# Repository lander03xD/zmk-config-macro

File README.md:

# macr03xD

## What is it?

This project is handwired macropad.

Project firmware is using [ZMK](https://zmk.dev).
The case and plate are modelled with [FreeCAD](https://www.freecad.org/).

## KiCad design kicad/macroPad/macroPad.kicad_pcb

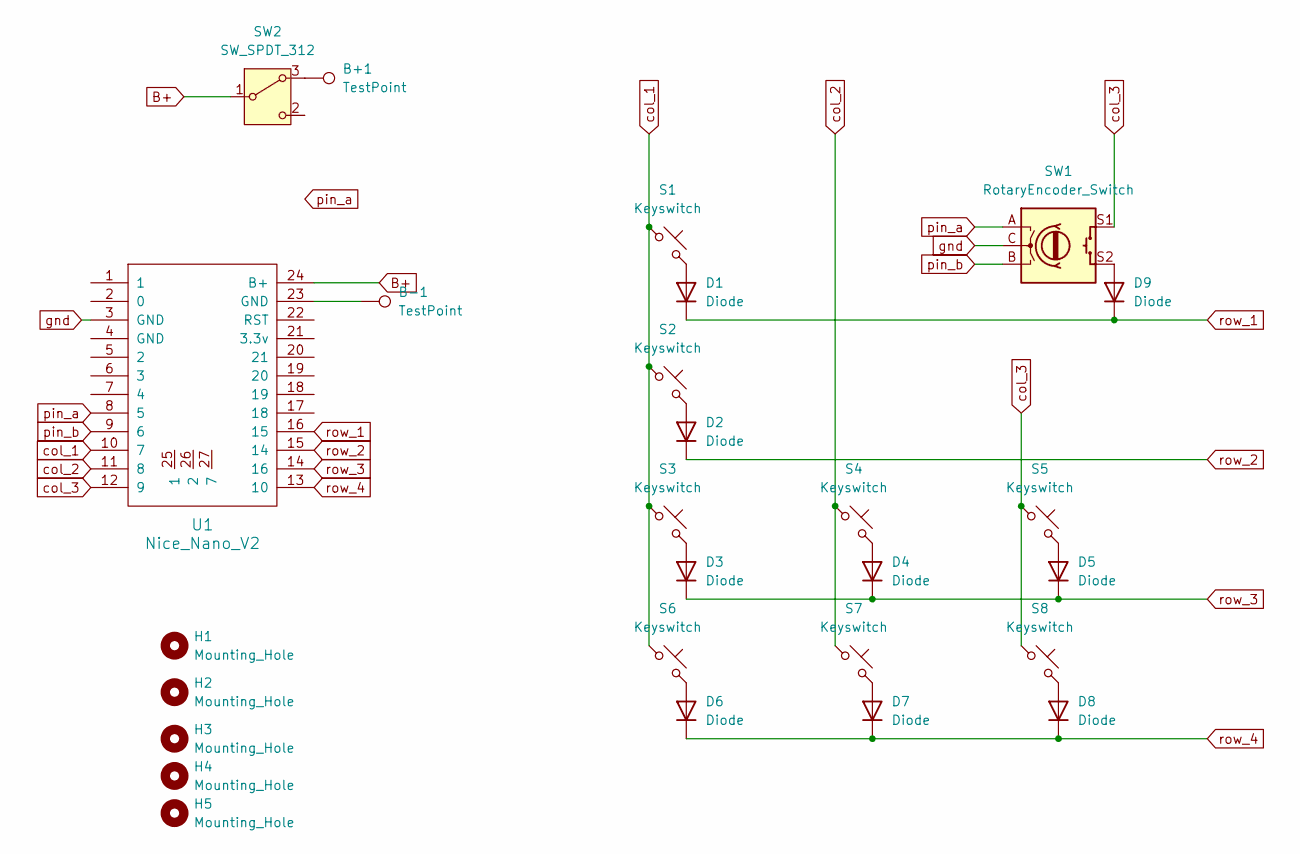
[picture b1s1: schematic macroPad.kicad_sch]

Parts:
B+1: TestPoint
B-1: TestPoint
D1, D2, D3, D4, D5, D6, D7, D8, D9: Diode; Diode_DO-35
H1, H2, H3, H4, H5: Mounting_Hole; MountingHole_2.2mm_M2
S1, S2, S3, S4, S5, S6, S7, S8: Keyswitch; MX_Solder_1.00u
SW1: RotaryEncoder_Switch; Encoder_EC11_MX
SW2: SW_SPDT_312; SW_Vertical_Slide_5mm
U1: Nice_Nano_V2

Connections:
B+: SW2.1 (B), U1.24 (B+)
unnamed: B-1.1, U1.23 (GND)
unnamed: D1.2 (A), S1.2
unnamed: D2.2 (A), S2.2
unnamed: D3.2 (A), S3.2
unnamed: D4.2 (A), S4.2
unnamed: D5.2 (A), S5.2
unnamed: D6.2 (A), S6.2
unnamed: D7.2 (A), S7.2
unnamed: D8.2 (A), S8.2
unnamed: D9.2 (A), SW1.S2
unnamed: B+1.1, SW2.3 (A)
col_1: S1.1, S2.1, S3.1, S6.1, U1.10 (7)
col_2: S4.1, S7.1, U1.11 (8)
col_3: S5.1, S8.1, SW1.S1, U1.12 (9)
gnd: SW1.C, U1.3 (GND)
pin_a: SW1.A, U1.8 (5)
pin_b: SW1.B, U1.9 (6)
row_1: D1.1 (K), D9.1 (K), U1.16 (15)
row_2: D2.1 (K), U1.15 (14)
row_3: D3.1 (K), D4.1 (K), D5.1 (K), U1.14 (16)
row_4: D6.1 (K), D7.1 (K), D8.1 (K), U1.13 (10)

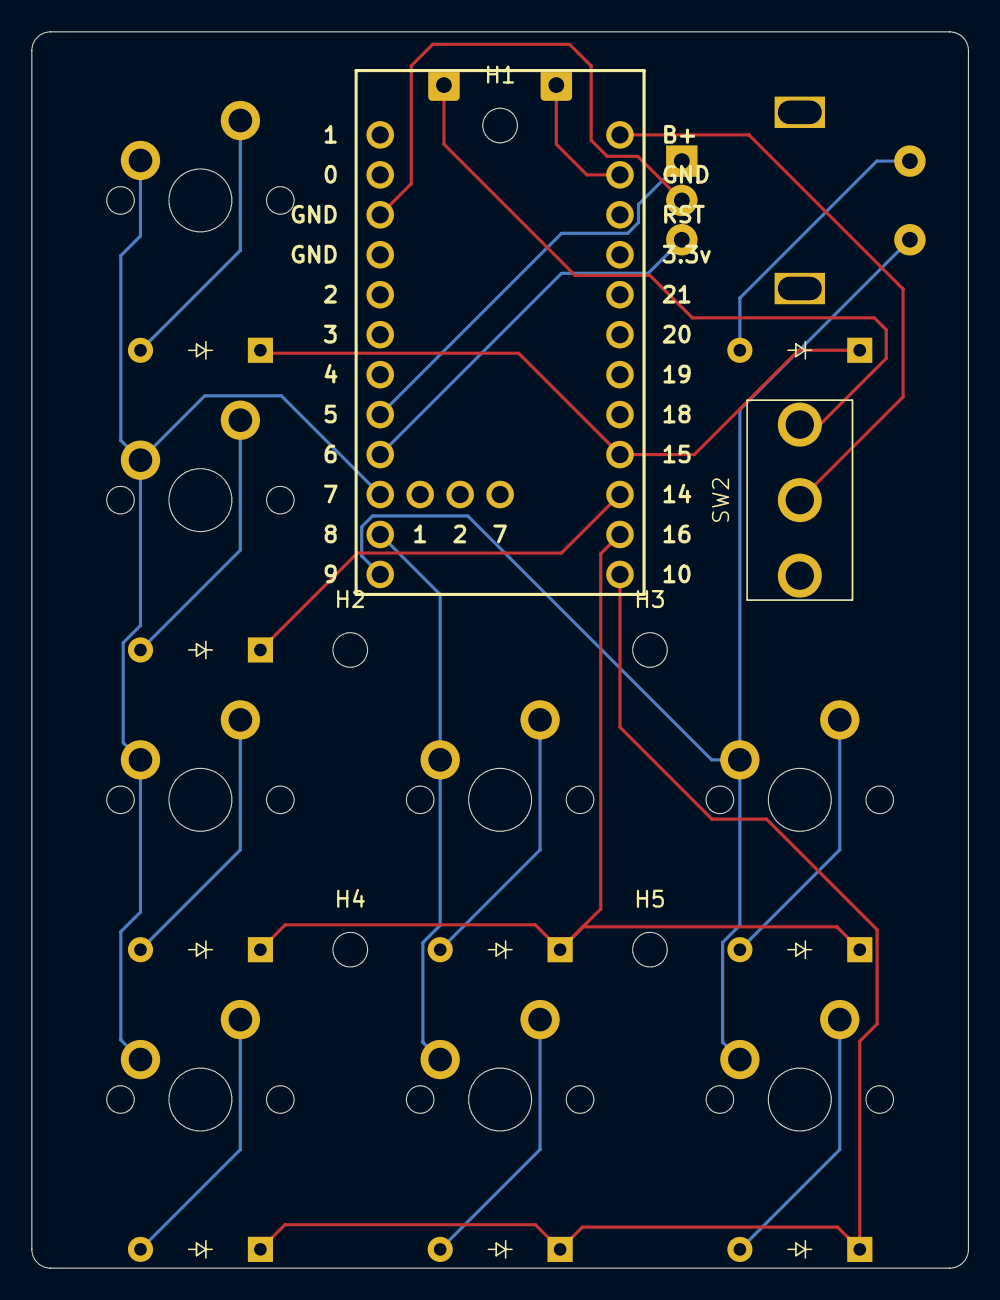
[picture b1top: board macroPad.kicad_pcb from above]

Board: 2 copper layers, 59.5 x 78.6 mm, 27 parts (0 on the bottom side), 22 nets.

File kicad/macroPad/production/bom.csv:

Designator,Footprint,Quantity,Value,LCSC Part #
"B+1, B-1",TestPoint,2,TestPoint,
"D1, D2, D3, D4, D5, D6, D7, D8, D9",Diode_DO-35,9,Diode,
"H1, H2, H3, H4, H5",MountingHole_2.2mm_M2,5,Mounting_Hole,
"S1, S2, S3, S4, S5, S6, S7, S8",MX_Solder_1.00u,8,Keyswitch,
SW1,Encoder_EC11_MX,1,RotaryEncoder_Switch,
SW2,SW_Vertical_Slide_5mm,1,SW_SPDT_312,
U1,Nice_Nano_V2,1,Nice_Nano_V2,

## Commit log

2025-05-08 Initial User Config.
2025-05-08 add bt clear for testing
2025-05-09 created keymap
2025-05-09 layers correction
2025-05-09 test cases
2025-05-09 tests complete
2025-05-09 attempt to add rotary encoder
2025-05-18 directwired
2025-05-18 remove breaking tab
2025-05-18 changed board to nice nano
2025-05-24 removed import
2025-05-24 added layout again
2025-05-24 added import again
2025-05-24 closed brackets
2025-05-24 pins
2025-05-24 configs
2025-05-24 overlay
2025-05-24 spelling mistake fix
2025-05-24 triggers-per-rotation
2025-05-24 steps
2025-05-24 retry
2025-05-25 different behaviors
2025-05-25 delected something
2025-05-25 removed config files
2025-05-25 reformated device tree
2025-05-25 added chosen sensors
2025-05-25 undo
2025-05-25 attempt to change gpio active
2025-05-25 back to high
2025-05-25 nkro full
2025-05-25 added reset key
2025-05-27 added space to restart build
2025-05-29 tests
2025-05-29 own thread
2025-05-29 readme.md
2025-05-29 images fix
2025-05-29 moved sensor-bindings into layers
2025-06-08 added macr03xD for seeed xiao board
2025-06-08 forgot semicolon
2025-06-08 forgot another semi
2025-06-08 refactor code to find bug
2025-06-08 changed to gpioX Y for the left encoder for the seeed xiao
2025-06-08 changed xiao_d labels everywhere
2025-06-08 other labels
2025-06-08 added 2 includes
2025-06-08 removed includes
2025-06-08 config mistake
2025-06-08 maybe use the right microcontroller you fucking monkey! I'm not that smart, trust me
2025-06-08 triggers update and matrix correction
2025-06-08 other rotation for encoder
2025-06-08 add zmk studio
2025-06-08 add zmk studio unlock
2025-06-09 change name and made reset
2025-06-15 ec11 changes and name change
2025-06-21 freecad case and plate for pcb version
2025-06-21 correct picture file format
2025-06-29 kicad stuff
2025-06-29 firmware for pcb version of macropad
2025-06-29 correct pin names
2025-06-30 added sticky layer for config
2025-07-25 correct overlay for mute button
